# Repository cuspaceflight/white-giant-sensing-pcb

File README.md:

# WG-sensing-pcb
PCB Design for WGData Acquisition via Current Loop Sensors

Current Design in KiCAD for 2x12 Sensors.

## Next Steps
- Create a separate Buck Converter board for a clean 5.4V DC supply
- Rework PCB Layout to only integrate some 5 sensors and test different designs

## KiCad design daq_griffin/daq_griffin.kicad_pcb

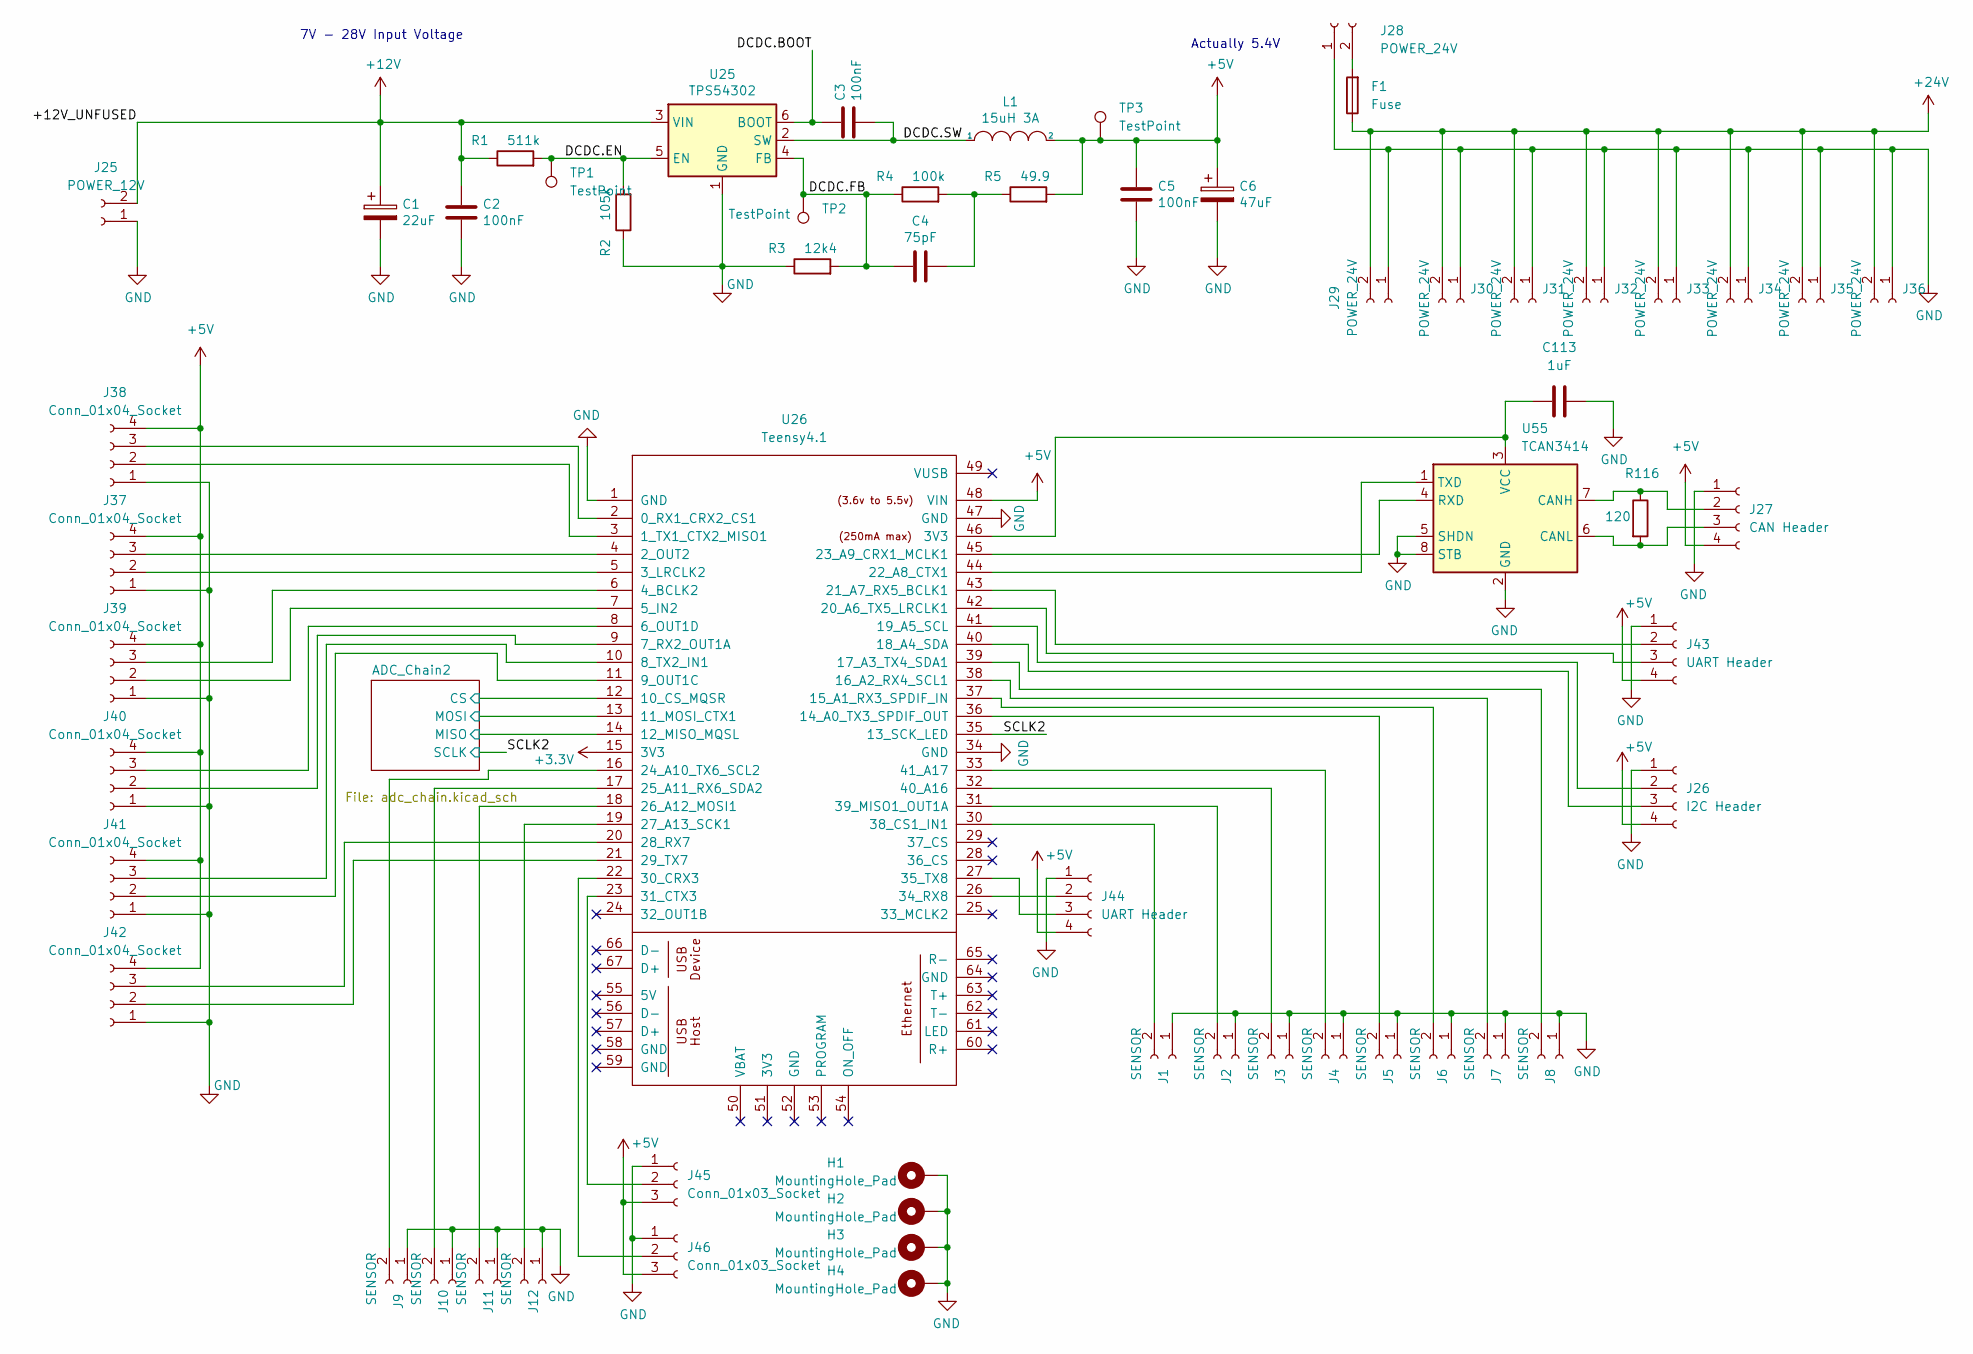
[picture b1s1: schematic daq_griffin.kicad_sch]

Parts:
C1: 22uF; C_0805_2012Metric_Pad1.18x1.45mm_HandSolder; Rating 25V; MPN generic C%f %v %r; LCSC C5674
C2, C3, C5: 100nF; C_0603_1608Metric_Pad1.08x0.95mm_HandSolder; MPN generic C%f %v %r; LCSC C1590
C4: 75pF; C_0603_1608Metric_Pad1.08x0.95mm_HandSolder; MPN generic C%f %v %r; LCSC C1681
C6: 47uF; C_0805_2012Metric_Pad1.18x1.45mm_HandSolder; Rating 6.3V; MPN generic C%f %v %r; LCSC C16780
C113: 1uF; C_0603_1608Metric_Pad1.08x0.95mm_HandSolder; LCSC C1592
F1: Fuse; Fuseholder_Cylinder-5x20mm_Stelvio-Kontek_PTF78_Horizontal_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
H1, H2, H3, H4: MountingHole_Pad; MountingHole_3.2mm_M3_Pad_Via
J1, J2, J3, J4, J5, J6, J7, J8, J9, J10, J11, J12: SENSOR; Molex_Nano-Fit_105309-xx02_1x02_P2.50mm_Vertical
J25: POWER_12V; Molex_Nano-Fit_105309-xx02_1x02_P2.50mm_Vertical
J26: I2C Header; Molex_Nano-Fit_105309-xx04_1x04_P2.50mm_Vertical
J27: CAN Header; Molex_Nano-Fit_105309-xx04_1x04_P2.50mm_Vertical
J28, J29, J30, J31, J32, J33, J34, J35, J36: POWER_24V; Molex_Nano-Fit_105309-xx02_1x02_P2.50mm_Vertical
J37, J38, J39, J40, J41, J42: Conn_01x04_Socket; JST_XH_B4B-XH-A_1x04_P2.50mm_Vertical
J43, J44: UART Header; Molex_Nano-Fit_105309-xx04_1x04_P2.50mm_Vertical
J45, J46: Conn_01x03_Socket; Molex_Nano-Fit_105309-xx03_1x03_P2.50mm_Vertical
L1: 15uH 3A; L_Bourns_SRN6045TA; MPN Bourns SRN8040TA-150M; LCSC C1330797
R1: 511k; R_0603_1608Metric_Pad0.98x0.95mm_HandSolder; MPN generic R%f %v %r; LCSC C188257
R2: 105k; R_0603_1608Metric_Pad0.98x0.95mm_HandSolder; MPN generic R%f %v %r; LCSC C16840
R3: 12k4; R_0603_1608Metric_Pad0.98x0.95mm_HandSolder; MPN generic R%f %v %r; LCSC C22865
R4: 100k; R_0603_1608Metric_Pad0.98x0.95mm_HandSolder; MPN generic R%f %v %r; LCSC C14675
R5: 49.9; R_0603_1608Metric_Pad0.98x0.95mm_HandSolder; MPN generic R%f %v %r; LCSC C23185
R116: 120; R_0603_1608Metric_Pad0.98x0.95mm_HandSolder; LCSC C22787
TP1, TP2, TP3: TestPoint; TestPoint_Pad_D1.0mm
U25: TPS54302; SOT-23-6; MPN TI TPS54302DDC; LCSC C129370
U26: Teensy4.1; Teensy41
U55: TCAN3414; SOIC-8_3.9x4.9mm_P1.27mm; LCSC C30111221

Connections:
+3.3V: U26.15 (3V3); also elsewhere on the board
+5V: C5.1, C6.1, J26.4, J27.4, J37.4, J38.4, J39.4, J40.4, J41.4, J42.4, J43.4, J44.4, J45.3, J46.3, L1.2, R5.2, TP3.1, U26.48 (VIN); also elsewhere on the board
+12V: C1.1, C2.1, J25.2, R1.1, U25.3 (VIN); also elsewhere on the board
+24V: F1.1, J29.2, J30.2, J31.2, J32.2, J33.2, J34.2, J35.2, J36.2
/ADC_Chain2/CS: U26.12 (10_CS_MQSR); also elsewhere on the board
/ADC_Chain2/MISO: U26.14 (12_MISO_MQSL); also elsewhere on the board
/ADC_Chain2/MOSI: U26.13 (11_MOSI_CTX1); also elsewhere on the board
/DCDC.BOOT: C3.1, U25.6 (BOOT)
/DCDC.EN: R1.2, R2.2, TP1.1, U25.5 (EN)
/DCDC.FB: C4.2, R3.2, R4.1, TP2.1, U25.4 (FB)
/DCDC.SW: C3.2, L1.1, U25.2 (SW)
/SCLK2: U26.35 (13_SCK_LED); also elsewhere on the board
GND: C1.2, C2.2, C5.2, C6.2, C113.2, H1.1, H2.1, H3.1, H4.1, J1.1, J2.1, J3.1, J4.1, J5.1, J6.1, J7.1, J8.1, J9.1, J10.1, J11.1, J12.1, J25.1, J26.1, J27.1, J28.1, J29.1, J30.1, J31.1, J32.1, J33.1, J34.1, J35.1, J36.1, J37.1, J38.1, J39.1, J40.1, J41.1, J42.1, J43.1, J44.1, J45.1, J46.1, R2.1, R3.1, U25.1 (GND), U26.1 (GND), U26.34 (GND), U26.47 (GND), U55.2 (GND), U55.5 (SHDN), U55.8 (STB); also elsewhere on the board
unnamed: C4.1, R4.2, R5.1
unnamed: J1.2, U26.30 (38_CS1_IN1)
unnamed: J2.2, U26.31 (39_MISO1_OUT1A)
unnamed: J3.2, U26.32 (40_A16)
unnamed: J4.2, U26.33 (41_A17)
unnamed: J5.2, U26.36 (14_A0_TX3_SPDIF_OUT)
unnamed: J6.2, U26.37 (15_A1_RX3_SPDIF_IN)
unnamed: J7.2, U26.38 (16_A2_RX4_SCL1)
unnamed: J8.2, U26.39 (17_A3_TX4_SDA1)
unnamed: J9.2, U26.16 (24_A10_TX6_SCL2)
unnamed: J10.2, U26.17 (25_A11_RX6_SDA2)
unnamed: J11.2, U26.18 (26_A12_MOSI1)
unnamed: J12.2, U26.19 (27_A13_SCK1)
unnamed: J26.2, U26.41 (19_A5_SCL)
unnamed: J26.3, U26.40 (18_A4_SDA)
unnamed: J27.2, R116.1, U55.7 (CANH)
unnamed: J27.3, R116.2, U55.6 (CANL)
unnamed: F1.2, J28.2
unnamed: J37.2, U26.5 (3_LRCLK2)
unnamed: J37.3, U26.4 (2_OUT2)
unnamed: J38.2, U26.3 (1_TX1_CTX2_MISO1)
unnamed: J38.3, U26.2 (0_RX1_CRX2_CS1)
unnamed: J39.2, U26.7 (5_IN2)
unnamed: J39.3, U26.6 (4_BCLK2)
unnamed: J40.2, U26.9 (7_RX2_OUT1A)
unnamed: J40.3, U26.8 (6_OUT1D)
unnamed: J41.2, U26.11 (9_OUT1C)
unnamed: J41.3, U26.10 (8_TX2_IN1)
unnamed: J42.2, U26.21 (29_TX7)
unnamed: J42.3, U26.20 (28_RX7)
unnamed: J43.2, U26.43 (21_A7_RX5_BCLK1)
unnamed: J43.3, U26.42 (20_A6_TX5_LRCLK1)
unnamed: J44.2, U26.26 (34_RX8)
unnamed: J44.3, U26.27 (35_TX8)
unnamed: J45.2, U26.23 (31_CTX3)
unnamed: J46.2, U26.22 (30_CRX3)
unnamed: U26.44 (22_A8_CTX1), U55.1 (TXD)
unnamed: U26.45 (23_A9_CRX1_MCLK1), U55.4 (RXD)
unnamed: C113.1, U26.46 (3V3), U55.3 (VCC)

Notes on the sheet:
Actually 5.4V
7V - 28V Input Voltage

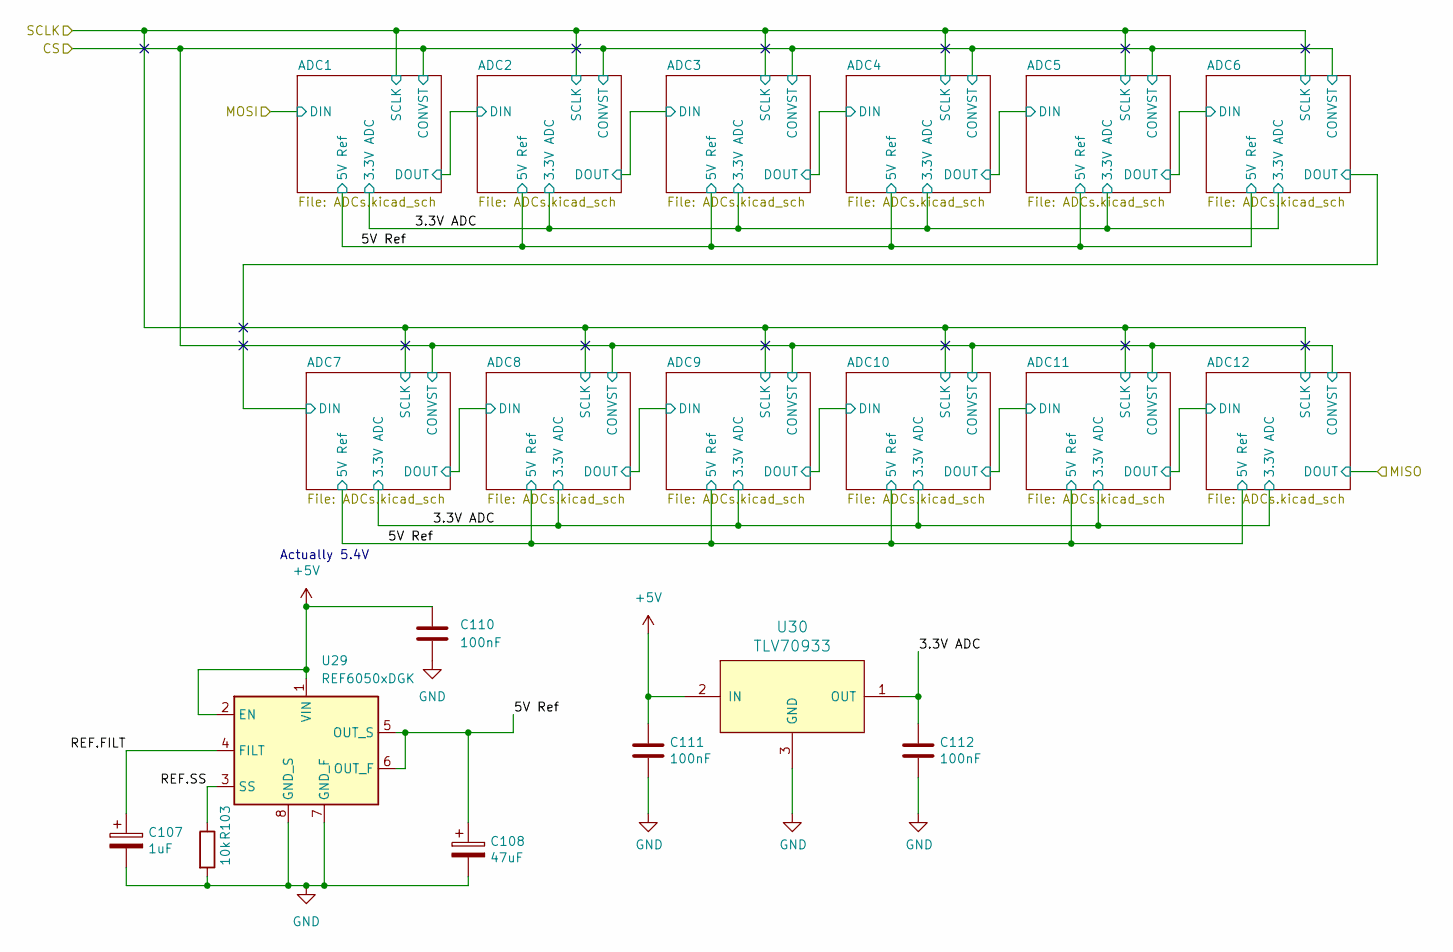
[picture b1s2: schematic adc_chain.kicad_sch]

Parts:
C107: 1uF; C_0603_1608Metric_Pad1.08x0.95mm_HandSolder; Rating 25V; MPN generic C%f %v %r; LCSC C1592
C108: 47uF; C_0805_2012Metric_Pad1.18x1.45mm_HandSolder; Rating 6.3V; MPN generic C%f %v %r; LCSC C16780
C110: 100nF; C_0603_1608Metric_Pad1.08x0.95mm_HandSolder; LCSC C1590
C111, C112: 100nF; C_0603_1608Metric_Pad1.08x0.95mm_HandSolder; MPN generic C%f %v %r; LCSC C1590
R103: 10k; R_0603_1608Metric_Pad0.98x0.95mm_HandSolder; MPN generic R%f %v %r; LCSC C15401
U29: REF6050xDGK; VSSOP-8_3.0x3.0mm_P0.65mm; LCSC C2157003
U30: TLV70933; SOT-23; MPN TI TLV76033DBZ; LCSC C133791

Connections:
+5V: C110.2, C111.1, U29.1 (VIN), U29.2 (EN), U30.2 (IN); also elsewhere on the board
/ADC_Chain2/3.3V ADC: C112.1, U30.1 (OUT); also elsewhere on the board
/ADC_Chain2/5V Ref: C108.1, U29.5 (OUT_S), U29.6 (OUT_F); also elsewhere on the board
/ADC_Chain2/REF.FILT: C107.1, U29.4 (FILT)
/ADC_Chain2/REF.SS: R103.1, U29.3 (SS)
GND: C107.2, C108.2, C110.1, C111.2, C112.2, R103.2, U29.7 (GND_F), U29.8 (GND_S), U30.3 (GND); also elsewhere on the board

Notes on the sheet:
Actually 5.4V

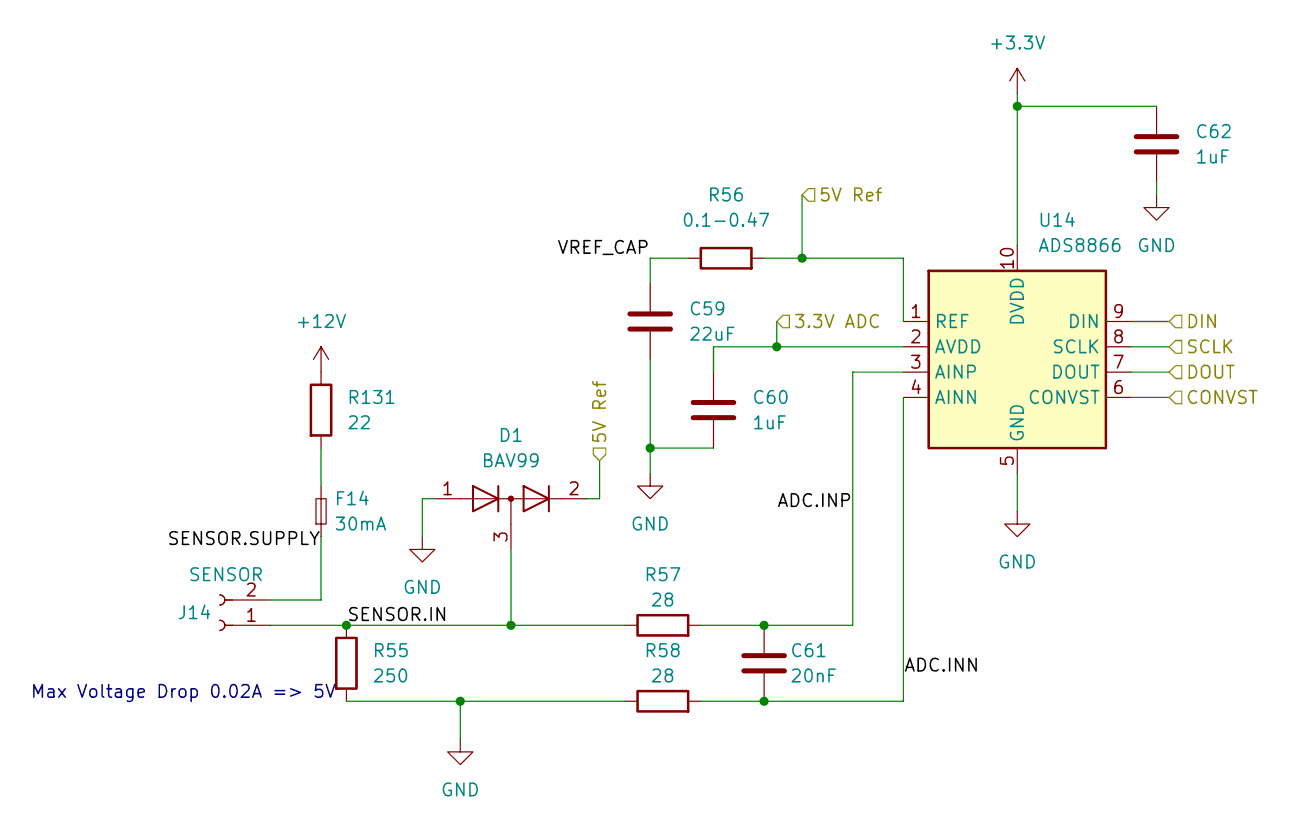
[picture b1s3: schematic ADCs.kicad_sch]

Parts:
C59: 22uF; C_0805_2012Metric_Pad1.18x1.45mm_HandSolder; LCSC C5674
C60, C62: 1uF; C_0603_1608Metric_Pad1.08x0.95mm_HandSolder; LCSC C1592
C61: 20nF; C_0603_1608Metric_Pad1.08x0.95mm_HandSolder; LCSC C307483
D1: BAV99; SOT-323_SC-70
F14: 30mA; Fuse_0603_1608Metric_Pad1.05x0.95mm_HandSolder; LCSC C914090
J14: SENSOR; Molex_Nano-Fit_105309-xx02_1x02_P2.50mm_Vertical
R55: 250; R_1206_3216Metric_Pad1.30x1.75mm_HandSolder; LCSC C2828898
R56: 0.1-0.47; R_0603_1608Metric_Pad0.98x0.95mm_HandSolder; LCSC C175686
R57, R58: 28; R_0603_1608Metric_Pad0.98x0.95mm_HandSolder; LCSC C217932
R131: 22; R_0603_1608Metric_Pad0.98x0.95mm_HandSolder; LCSC C1203
U14: ADS8866; VSSOP-10_3x3mm_P0.5mm; LCSC C455432

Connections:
+3.3V: C62.1, U14.10 (DVDD); also elsewhere on the board
+12V: R131.1; also elsewhere on the board
/ADC_Chain2/3.3V ADC: C60.1, U14.2 (AVDD); also elsewhere on the board
/ADC_Chain2/5V Ref: D1.2 (A), R56.2, U14.1 (REF); also elsewhere on the board
/ADC_Chain2/ADC1/DOUT: U14.9 (DIN); also elsewhere on the board
/ADC_Chain2/ADC2/ADC.INN: C61.2, R58.2, U14.4 (AINN)
/ADC_Chain2/ADC2/ADC.INP: C61.1, R57.2, U14.3 (AINP)
/ADC_Chain2/ADC2/DOUT: U14.7 (DOUT); also elsewhere on the board
/ADC_Chain2/ADC2/SENSOR.IN: D1.3 (K), J14.1, R55.1, R57.1
/ADC_Chain2/ADC2/SENSOR.SUPPLY: F14.1, J14.2
/ADC_Chain2/ADC2/VREF_CAP: C59.1, R56.1
/ADC_Chain2/CS: U14.6 (CONVST); also elsewhere on the board
/SCLK2: U14.8 (SCLK); also elsewhere on the board
GND: C59.2, C60.2, C62.2, D1.1 (K), R55.2, R58.1, U14.5 (GND); also elsewhere on the board
unnamed: F14.2, R131.2

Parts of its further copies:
C63, C67, C71, C75, C79, C83, C87, C91, C95, C99, C103: 22uF; C_0805_2012Metric_Pad1.18x1.45mm_HandSolder; LCSC C5674
C64, C66, C68, C70, C72, C74, C76, C78, C80, C82, C84, C86, C88, C90, C92, C94, C96, C98, C100, C102, C104, C106: 1uF; C_0603_1608Metric_Pad1.08x0.95mm_HandSolder; LCSC C1592
C65, C69, C73, C77, C81, C85, C89, C93, C97, C101, C105: 20nF; C_0603_1608Metric_Pad1.08x0.95mm_HandSolder; LCSC C307483
D2, D3, D4, D5, D6, D7, D8, D9, D10, D11, D12: BAV99; SOT-323_SC-70
F13, F15, F16, F17, F18, F19, F20, F21, F22, F23, F24: 30mA; Fuse_0603_1608Metric_Pad1.05x0.95mm_HandSolder; LCSC C914090
J13, J15, J16, J17, J18, J19, J20, J21, J22, J23, J24: SENSOR; Molex_Nano-Fit_105309-xx02_1x02_P2.50mm_Vertical
R59, R63, R67, R71, R75, R79, R83, R87, R91, R95, R99: 250; R_1206_3216Metric_Pad1.30x1.75mm_HandSolder; LCSC C2828898
R60, R64, R68, R72, R76, R80, R84, R88, R92, R96, R100: 0.1-0.47; R_0603_1608Metric_Pad0.98x0.95mm_HandSolder; LCSC C175686
R61, R62, R65, R66, R69, R70, R73, R74, R77, R78, R81, R82, R85, R86, R89, R90, R93, R94, R97, R98, R101, R102: 28; R_0603_1608Metric_Pad0.98x0.95mm_HandSolder; LCSC C217932
R130, R132, R133, R134, R135, R136, R137, R138, R139, R140, R141: 22; R_0603_1608Metric_Pad0.98x0.95mm_HandSolder; LCSC C1203
U13, U15, U16, U17, U18, U19, U20, U21, U22, U23, U24: ADS8866; VSSOP-10_3x3mm_P0.5mm; LCSC C455432

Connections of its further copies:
+3.3V: C66.1, C70.1, C74.1, C78.1, C82.1, C86.1, C90.1, C94.1, C98.1, C102.1, C106.1, U13.10 (DVDD), U15.10 (DVDD), U16.10 (DVDD), U17.10 (DVDD), U18.10 (DVDD), U19.10 (DVDD), U20.10 (DVDD), U21.10 (DVDD), U22.10 (DVDD), U23.10 (DVDD), U24.10 (DVDD); also elsewhere on the board
+12V: R130.1, R132.1, R133.1, R134.1, R135.1, R136.1, R137.1, R138.1, R139.1, R140.1, R141.1; also elsewhere on the board
/ADC_Chain2/3.3V ADC: C64.1, C68.1, C72.1, C76.1, C80.1, C84.1, C88.1, C92.1, C96.1, C100.1, C104.1, U13.2 (AVDD), U15.2 (AVDD), U16.2 (AVDD), U17.2 (AVDD), U18.2 (AVDD), U19.2 (AVDD), U20.2 (AVDD), U21.2 (AVDD), U22.2 (AVDD), U23.2 (AVDD), U24.2 (AVDD); also elsewhere on the board
/ADC_Chain2/5V Ref: D2.2 (A), D3.2 (A), D4.2 (A), D5.2 (A), D6.2 (A), D7.2 (A), D8.2 (A), D9.2 (A), D10.2 (A), D11.2 (A), D12.2 (A), R60.2, R64.2, R68.2, R72.2, R76.2, R80.2, R84.2, R88.2, R92.2, R96.2, R100.2, U13.1 (REF), U15.1 (REF), U16.1 (REF), U17.1 (REF), U18.1 (REF), U19.1 (REF), U20.1 (REF), U21.1 (REF), U22.1 (REF), U23.1 (REF), U24.1 (REF); also elsewhere on the board
/ADC_Chain2/ADC1/ADC.INN: C69.2, R66.2, U13.4 (AINN)
/ADC_Chain2/ADC1/ADC.INP: C69.1, R65.2, U13.3 (AINP)
/ADC_Chain2/ADC1/DOUT: U13.7 (DOUT); also elsewhere on the board
/ADC_Chain2/ADC1/SENSOR.IN: D3.3 (K), J13.1, R63.1, R65.1
/ADC_Chain2/ADC1/SENSOR.SUPPLY: F13.1, J13.2
/ADC_Chain2/ADC1/VREF_CAP: C67.1, R64.1
/ADC_Chain2/ADC2/DOUT: U15.9 (DIN); also elsewhere on the board
/ADC_Chain2/ADC3/ADC.INN: C65.2, R62.2, U15.4 (AINN)
/ADC_Chain2/ADC3/ADC.INP: C65.1, R61.2, U15.3 (AINP)
/ADC_Chain2/ADC3/DOUT: U15.7 (DOUT), U16.9 (DIN)
/ADC_Chain2/ADC3/SENSOR.IN: D2.3 (K), J15.1, R59.1, R61.1
/ADC_Chain2/ADC3/SENSOR.SUPPLY: F15.1, J15.2
/ADC_Chain2/ADC3/VREF_CAP: C63.1, R60.1
/ADC_Chain2/ADC4/ADC.INN: C101.2, R98.2, U16.4 (AINN)
/ADC_Chain2/ADC4/ADC.INP: C101.1, R97.2, U16.3 (AINP)
/ADC_Chain2/ADC4/DOUT: U16.7 (DOUT), U17.9 (DIN)
/ADC_Chain2/ADC4/SENSOR.IN: D11.3 (K), J16.1, R95.1, R97.1
/ADC_Chain2/ADC4/SENSOR.SUPPLY: F16.1, J16.2
/ADC_Chain2/ADC4/VREF_CAP: C99.1, R96.1
/ADC_Chain2/ADC5/ADC.INN: C73.2, R70.2, U17.4 (AINN)
/ADC_Chain2/ADC5/ADC.INP: C73.1, R69.2, U17.3 (AINP)
/ADC_Chain2/ADC5/DOUT: U17.7 (DOUT), U18.9 (DIN)
/ADC_Chain2/ADC5/SENSOR.IN: D4.3 (K), J17.1, R67.1, R69.1
/ADC_Chain2/ADC5/SENSOR.SUPPLY: F17.1, J17.2
/ADC_Chain2/ADC5/VREF_CAP: C71.1, R68.1
/ADC_Chain2/ADC6/ADC.INN: C77.2, R74.2, U18.4 (AINN)
/ADC_Chain2/ADC6/ADC.INP: C77.1, R73.2, U18.3 (AINP)
/ADC_Chain2/ADC6/DOUT: U18.7 (DOUT), U19.9 (DIN)
/ADC_Chain2/ADC6/SENSOR.IN: D5.3 (K), J18.1, R71.1, R73.1
/ADC_Chain2/ADC6/SENSOR.SUPPLY: F18.1, J18.2
/ADC_Chain2/ADC6/VREF_CAP: C75.1, R72.1
/ADC_Chain2/ADC7/ADC.INN: C81.2, R78.2, U19.4 (AINN)
/ADC_Chain2/ADC7/ADC.INP: C81.1, R77.2, U19.3 (AINP)
/ADC_Chain2/ADC7/DOUT: U19.7 (DOUT), U20.9 (DIN)
/ADC_Chain2/ADC7/SENSOR.IN: D6.3 (K), J19.1, R75.1, R77.1
/ADC_Chain2/ADC7/SENSOR.SUPPLY: F19.1, J19.2
/ADC_Chain2/ADC7/VREF_CAP: C79.1, R76.1
/ADC_Chain2/ADC8/ADC.INN: C85.2, R82.2, U20.4 (AINN)
/ADC_Chain2/ADC8/ADC.INP: C85.1, R81.2, U20.3 (AINP)
/ADC_Chain2/ADC8/DOUT: U20.7 (DOUT), U21.9 (DIN)
/ADC_Chain2/ADC8/SENSOR.IN: D7.3 (K), J20.1, R79.1, R81.1
/ADC_Chain2/ADC8/SENSOR.SUPPLY: F20.1, J20.2
/ADC_Chain2/ADC8/VREF_CAP: C83.1, R80.1
/ADC_Chain2/ADC9/ADC.INN: C89.2, R86.2, U21.4 (AINN)
/ADC_Chain2/ADC9/ADC.INP: C89.1, R85.2, U21.3 (AINP)
/ADC_Chain2/ADC9/SENSOR.IN: D8.3 (K), J21.1, R83.1, R85.1
/ADC_Chain2/ADC9/SENSOR.SUPPLY: F21.1, J21.2
/ADC_Chain2/ADC9/VREF_CAP: C87.1, R84.1
/ADC_Chain2/ADC10/ADC.INN: C93.2, R90.2, U22.4 (AINN)
/ADC_Chain2/ADC10/ADC.INP: C93.1, R89.2, U22.3 (AINP)
/ADC_Chain2/ADC10/DIN: U21.7 (DOUT), U22.9 (DIN)
/ADC_Chain2/ADC10/DOUT: U22.7 (DOUT), U23.9 (DIN)
/ADC_Chain2/ADC10/SENSOR.IN: D9.3 (K), J22.1, R87.1, R89.1
/ADC_Chain2/ADC10/SENSOR.SUPPLY: F22.1, J22.2
/ADC_Chain2/ADC10/VREF_CAP: C91.1, R88.1
/ADC_Chain2/ADC11/ADC.INN: C97.2, R94.2, U23.4 (AINN)
/ADC_Chain2/ADC11/ADC.INP: C97.1, R93.2, U23.3 (AINP)
/ADC_Chain2/ADC11/DOUT: U23.7 (DOUT), U24.9 (DIN)
/ADC_Chain2/ADC11/SENSOR.IN: D10.3 (K), J23.1, R91.1, R93.1
/ADC_Chain2/ADC11/SENSOR.SUPPLY: F23.1, J23.2
/ADC_Chain2/ADC11/VREF_CAP: C95.1, R92.1
/ADC_Chain2/ADC12/ADC.INN: C105.2, R102.2, U24.4 (AINN)
/ADC_Chain2/ADC12/ADC.INP: C105.1, R101.2, U24.3 (AINP)
/ADC_Chain2/ADC12/SENSOR.IN: D12.3 (K), J24.1, R99.1, R101.1
/ADC_Chain2/ADC12/SENSOR.SUPPLY: F24.1, J24.2
/ADC_Chain2/ADC12/VREF_CAP: C103.1, R100.1
/ADC_Chain2/CS: U13.6 (CONVST), U15.6 (CONVST), U16.6 (CONVST), U17.6 (CONVST), U18.6 (CONVST), U19.6 (CONVST), U20.6 (CONVST), U21.6 (CONVST), U22.6 (CONVST), U23.6 (CONVST), U24.6 (CONVST); also elsewhere on the board
/ADC_Chain2/MISO: U24.7 (DOUT); also elsewhere on the board
/ADC_Chain2/MOSI: U13.9 (DIN); also elsewhere on the board
/SCLK2: U13.8 (SCLK), U15.8 (SCLK), U16.8 (SCLK), U17.8 (SCLK), U18.8 (SCLK), U19.8 (SCLK), U20.8 (SCLK), U21.8 (SCLK), U22.8 (SCLK), U23.8 (SCLK), U24.8 (SCLK); also elsewhere on the board
GND: C63.2, C64.2, C66.2, C67.2, C68.2, C70.2, C71.2, C72.2, C74.2, C75.2, C76.2, C78.2, C79.2, C80.2, C82.2, C83.2, C84.2, C86.2, C87.2, C88.2, C90.2, C91.2, C92.2, C94.2, C95.2, C96.2, C98.2, C99.2, C100.2, C102.2, C103.2, C104.2, C106.2, D2.1 (K), D3.1 (K), D4.1 (K), D5.1 (K), D6.1 (K), D7.1 (K), D8.1 (K), D9.1 (K), D10.1 (K), D11.1 (K), D12.1 (K), R59.2, R62.1, R63.2, R66.1, R67.2, R70.1, R71.2, R74.1, R75.2, R78.1, R79.2, R82.1, R83.2, R86.1, R87.2, R90.1, R91.2, R94.1, R95.2, R98.1, R99.2, R102.1, U13.5 (GND), U15.5 (GND), U16.5 (GND), U17.5 (GND), U18.5 (GND), U19.5 (GND), U20.5 (GND), U21.5 (GND), U22.5 (GND), U23.5 (GND), U24.5 (GND); also elsewhere on the board
unnamed: F13.2, R130.2
unnamed: F15.2, R132.2
unnamed: F16.2, R133.2
unnamed: F17.2, R134.2
unnamed: F18.2, R135.2
unnamed: F19.2, R136.2
unnamed: F20.2, R137.2
unnamed: F21.2, R138.2
unnamed: F22.2, R139.2
unnamed: F23.2, R140.2
unnamed: F24.2, R141.2

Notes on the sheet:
Max Voltage Drop 0.02A => 5V

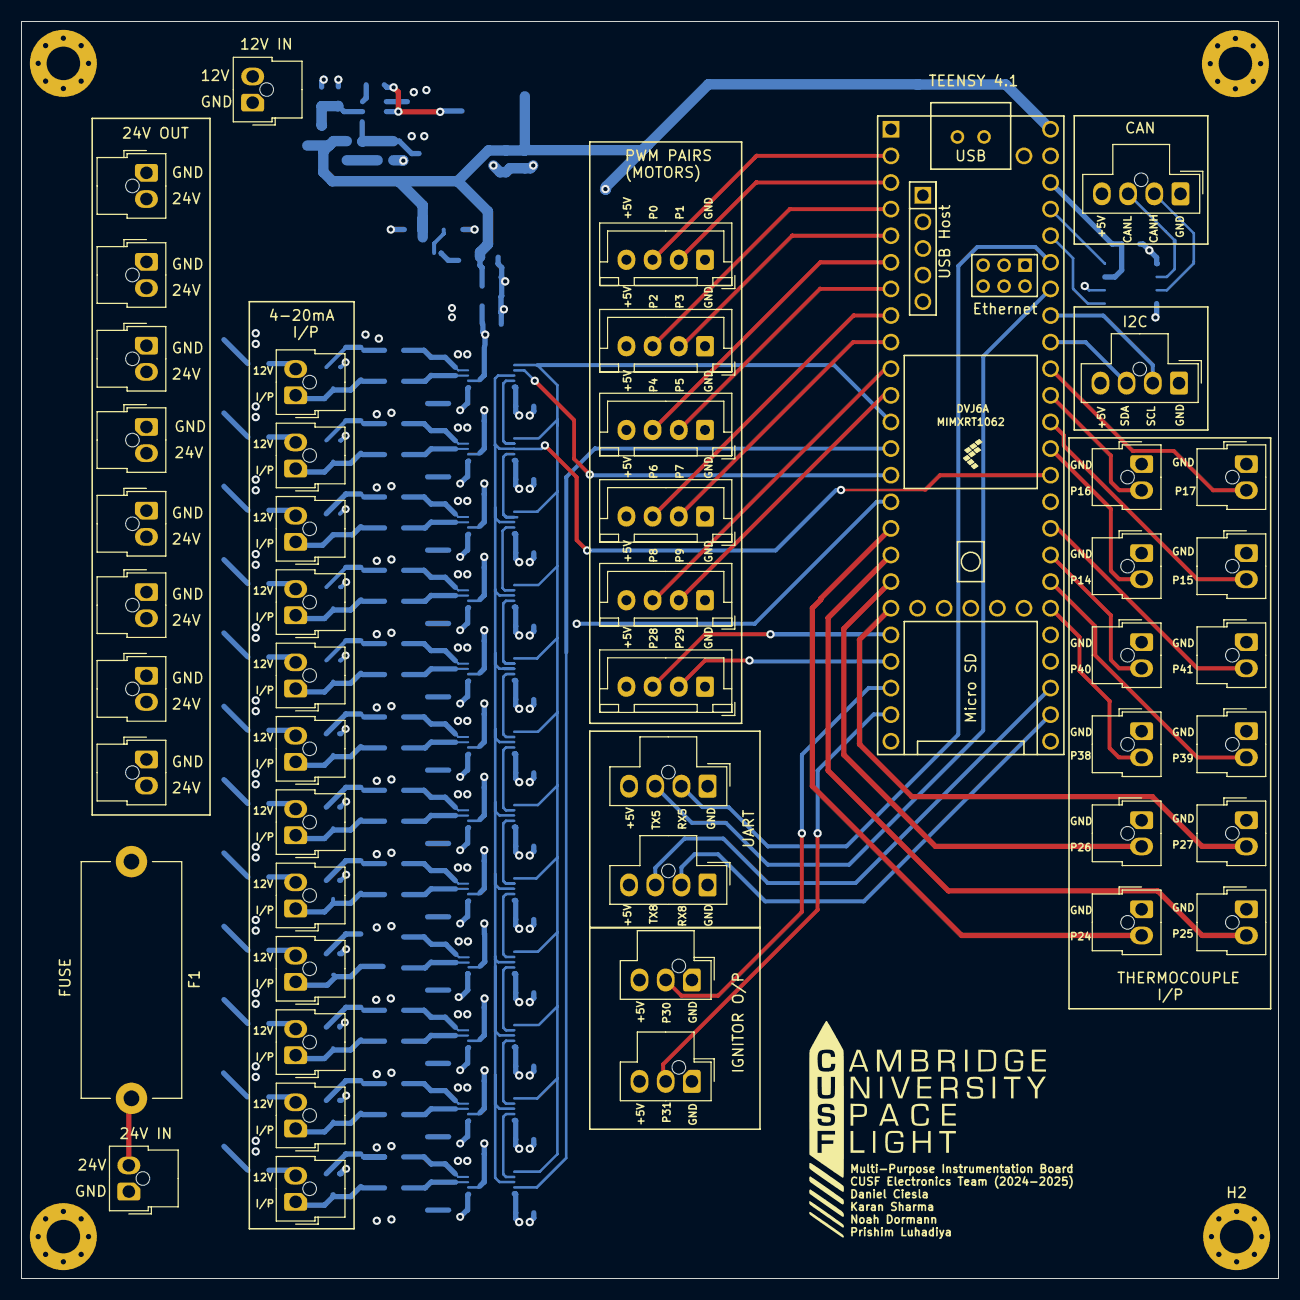
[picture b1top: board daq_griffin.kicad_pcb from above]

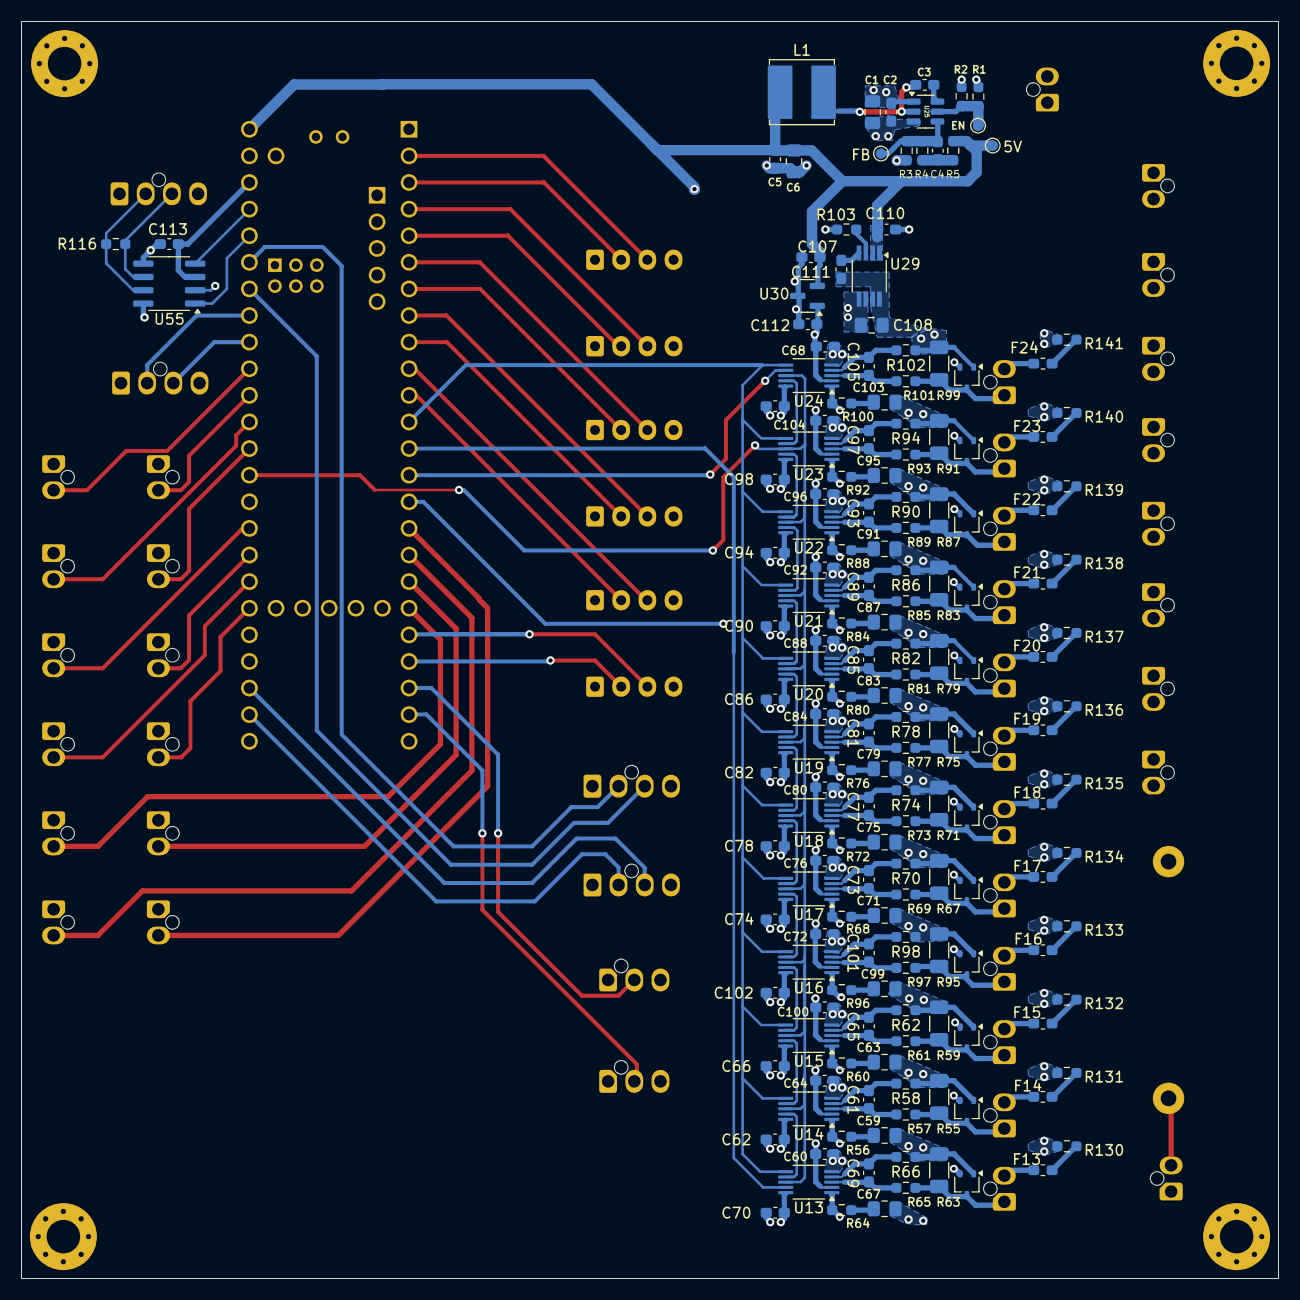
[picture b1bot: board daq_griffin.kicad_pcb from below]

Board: 4 copper layers, 120.0 x 120.0 mm, 223 parts (171 on the bottom side), 139 nets.

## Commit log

2024-11-22 Add files via upload
    one 5 V plane contained only 2 connections, so it was replaced with a single wire
2024-12-07 Add thermocouple connectors and minor layout changes.
2024-12-08 Change CUSF logo to F Silkscreen from User layer
2025-02-09 Add 24V capability, add feed systems motor connections, fix SPI connections, add ignitor board connections, add i2c connections.
2025-02-11 Rewired right side and fixed dual transistor
2025-02-23 Complete Silkscreen
2025-03-02 Final touches to silkscreen and hole clearance, names added
2025-03-23 Move 12V - 5V converter circuit to back of board.
2025-04-24 Inductor footprint changed, ADC fuse value now 30mA, ADC 25R resistor now 22R, 0.1-0.47R resistor set to 0.47R
2025-04-25 Added JLCPCB part numbers to all back side components to be in PCBA
